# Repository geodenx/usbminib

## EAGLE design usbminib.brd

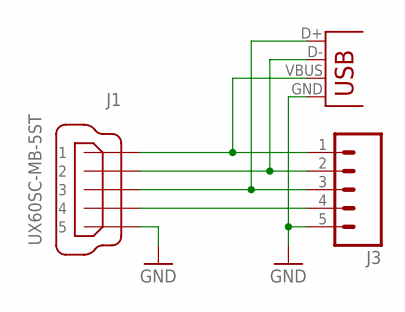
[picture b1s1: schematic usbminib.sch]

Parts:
J1: UX60SC-MB-5ST
J2: USB-A-H
J3: M05PTH; 1X05

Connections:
GND: J1.5, J2.GND, J3.5
unnamed: J1.2, J2.D-, J3.2
unnamed: J1.3, J2.D+, J3.3
unnamed: J1.4, J3.4
VBUS: J1.1, J2.VBUS, J3.1

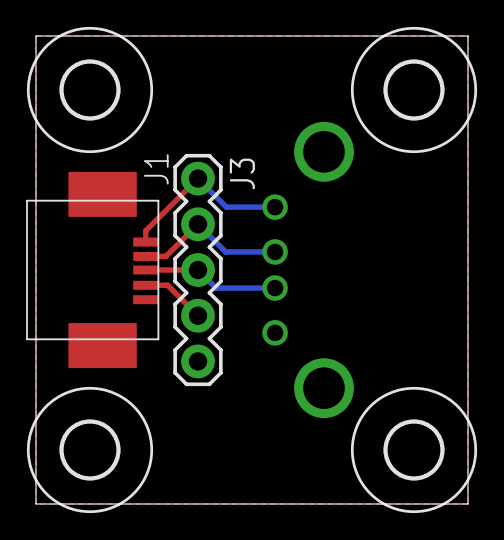
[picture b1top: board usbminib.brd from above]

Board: 2 copper layers, 24.0 x 26.0 mm, 7 parts (1 on the bottom side), 5 nets.

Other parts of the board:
U$2, U$3, U$4, U$5: 3,0

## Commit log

2013-02-02 initial
2013-02-03 Add USB-A connector, two holes
2013-02-03 Replace USB-A SMD with USB-A Through Via
2013-02-03 Widen GND/VBUS clearance
2013-04-05 Generate gerber files and add gerbv project file

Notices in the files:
parts and their libraries:
SparkFun: Licensing: CC v3.0 Share-Alike You are welcome to use this library for commercial purposes.
